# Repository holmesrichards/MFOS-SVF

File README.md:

# MFOS-SVF
Eurorack adaptation of the MFOS "Oldie But Goody" state variable filter

This is a Eurorack version of a state variable voltage controlled filter by Ray Wilson of musicfromouterspace.com. At that site there is a state variable VCF listed under "Analog Synthesizer Modules" but this project is based on another, earlier design listed under "Oldies But Goodies" at http://musicfromouterspace.com/index.php?MAINTAB=SYNTHDIY&PROJARG=OLDIESBUTGOODIES/VCF/vcfstatevar.html&VPW=2087&VPH=905.

Wilson's design was for a module in his own preferred format, with ±12V and ground soldered to the board and panel hardware mounted to the panel and wired to the board. This version has a Eurorack power connector and has panel hardware mounted to a panel PCB coupled to a main PCB with most of the circuitry.

Included in this repository are KiCad-format schematics and PCB designs for the two circuit boards, as well as an Inkscape .svg file for the panel design and a KiCad-format "PCB" for fabrication of the panel by a PCB company.

The schematics are closely based upon Wilson's original and are governed by licensing information at http://musicfromouterspace.com. The PCB layouts and panel design are new, by Richard Holmes.

BOMs are here:
https://github.com/holmesrichards/MFOS-SVF/blob/master/OBG-SVF-mainPCB/OBG-SVF-mainpcb_bom.md
and here:
https://github.com/holmesrichards/MFOS-SVF/blob/master/OBG-SVF-panelPCB/OBG-SVF-panelpcb_bom.md

## Build notes

Pretty standard. Panel PCB and main PCB joined with 2x6 pin header/socket. Use two 10 mm M3 spacers and four M3 screws to hold them together.

This time most of the components go on the panel-facing side. The power header and trimmer go on the other side. I intended the electrolytics to go on the panel-facing side but mine were too tall to fit between the boards so I mounted them on the other side.

The trimmer adjusts V/Oct response. Adjust it so a change of 1 octave (1V) on the CV input results in a change of 18 mV at the base of Q1.

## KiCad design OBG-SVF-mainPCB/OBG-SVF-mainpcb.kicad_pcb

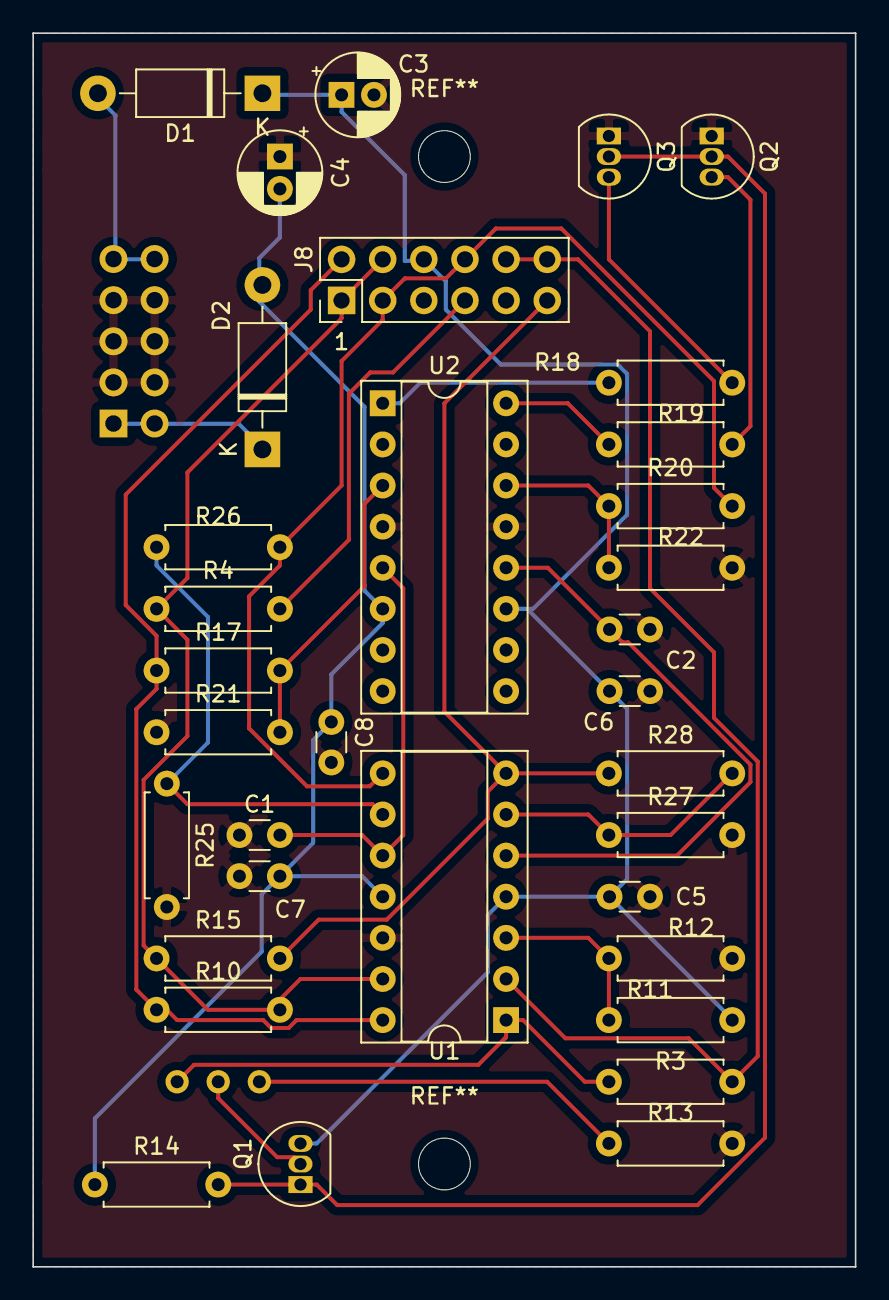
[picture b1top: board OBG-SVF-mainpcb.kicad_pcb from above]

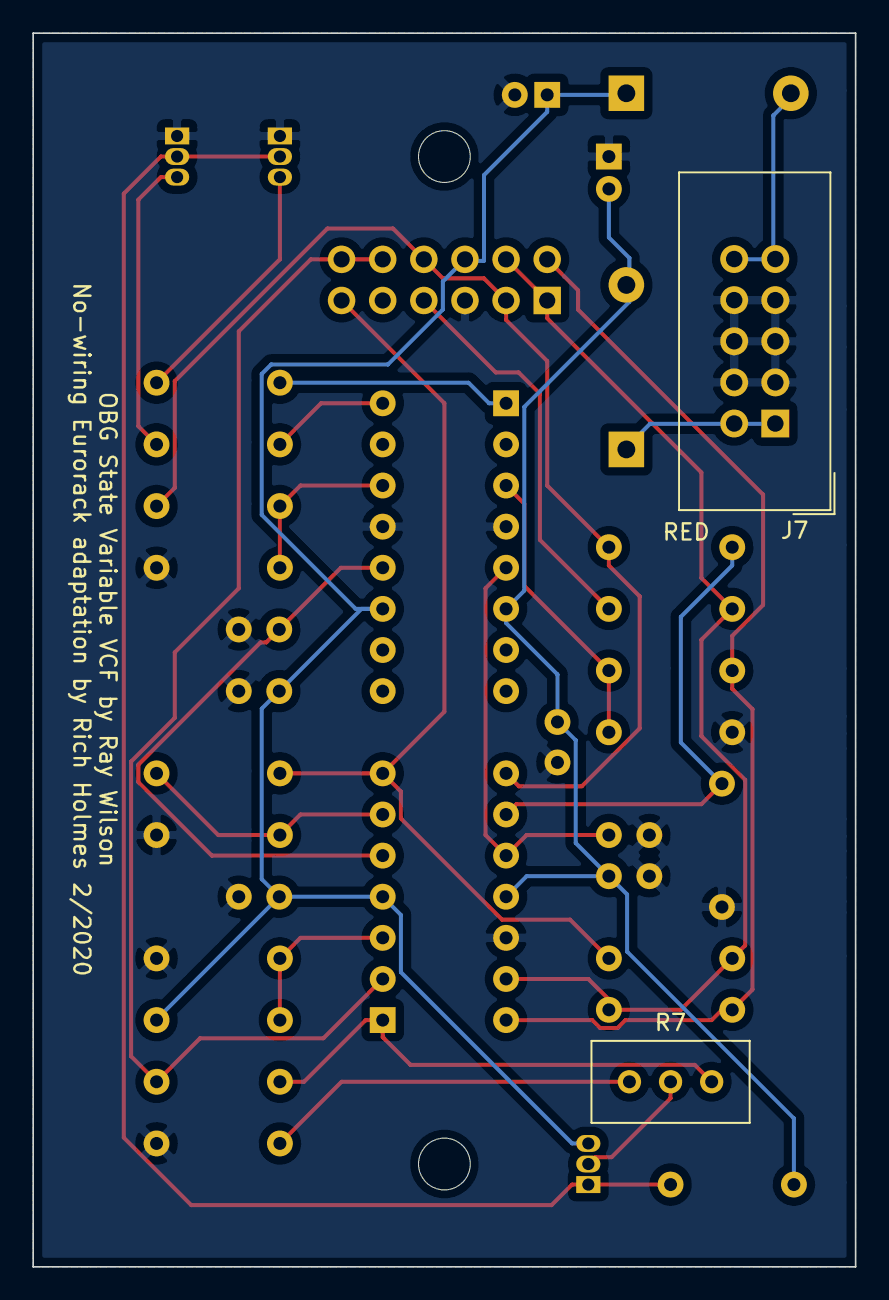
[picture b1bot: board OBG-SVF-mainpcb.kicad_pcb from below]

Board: 2 copper layers, 50.8 x 76.2 mm, 36 parts (2 on the bottom side), 26 nets.

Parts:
C1, C2: 470pF; C_Disc_D3.0mm_W1.6mm_P2.50mm
C3, C4: 10U; CP_Radial_D5.0mm_P2.00mm
C5, C6, C7, C8: 0.01U; C_Disc_D3.0mm_W1.6mm_P2.50mm
D1, D2: 1N5817; D_DO-41_SOD81_P10.16mm_Horizontal
J7: EURO_PWR_2x5; Eurorack_Power_Header_Shrouded
J8: Conn_02x06_Odd_Even; PinHeader_2x06_P2.54mm_Vertical
Q1: 2N3904; TO-92_Inline
Q2, Q3: 2N3906; TO-92_Inline
R3, R12: 2k; R_Axial_DIN0207_L6.3mm_D2.5mm_P7.62mm_Horizontal
R4, R10, R15: 47k; R_Axial_DIN0207_L6.3mm_D2.5mm_P7.62mm_Horizontal
R7: 100R; Potentiometer_Bourns_3296W_Vertical
R11, R17, R20: 100k; R_Axial_DIN0207_L6.3mm_D2.5mm_P7.62mm_Horizontal
R13: 470R; R_Axial_DIN0207_L6.3mm_D2.5mm_P7.62mm_Horizontal
R14: 120k; R_Axial_DIN0207_L6.3mm_D2.5mm_P7.62mm_Horizontal
R18, R19: 20k; R_Axial_DIN0207_L6.3mm_D2.5mm_P7.62mm_Horizontal
R21, R22: 1k; R_Axial_DIN0207_L6.3mm_D2.5mm_P7.62mm_Horizontal
R25, R27: 39k; R_Axial_DIN0207_L6.3mm_D2.5mm_P7.62mm_Horizontal
R26, R28: 150k; R_Axial_DIN0207_L6.3mm_D2.5mm_P7.62mm_Horizontal
U1: TL084; DIP-14_W7.62mm_Socket
U2: LM13700; DIP-16_W7.62mm_Socket

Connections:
+12V: C3.1, C5.2, C6.2, D1.1, J8.6, Q1.3, R11.2, U1.4, U2.11
-12V: C4.2, C7.1, C8.1, D2.2, R14.1, U1.11, U2.6
/VC: Q1.1, Q2.2, Q3.2, R14.2
BP: J8.3, J8.8, R20.2, R26.1, U1.8
CVIn: J8.10, J8.12, R3.2, U1.2
GND: C1.2, C2.1, C3.2, C4.1, C5.1, C6.1, C7.2, C8.2, J7.3, J7.4, J7.5, J7.6, J7.7, J7.8, J8.5, Q2.1, Q3.1, R12.1, R13.1, R21.1, R22.1, R25.2, R27.2, U1.12, U2.4, U2.13
HP: J8.2, R10.1, R17.1, U1.14
LP: J8.11, R15.2, R28.1, U1.7
unnamed: C1.1, U1.10, U2.5
unnamed: C2.2, U1.5, U2.12
unnamed: D1.2, J7.9, J7.10
unnamed: D2.1, J7.1, J7.2
unnamed: Q1.2, R7.2
unnamed: Q2.3, R19.1
unnamed: Q3.3, R18.1
unnamed: R3.1, R7.1, U1.1
unnamed: R11.1, R12.2, U1.3
unnamed: R7.3, R13.2
unnamed: R17.2, R21.2, U2.3
unnamed: R18.2, U2.1
unnamed: R19.2, U2.16
unnamed: R20.1, R22.2, U2.14
unnamed: R25.1, R26.2, U1.9
unnamed: R27.1, R28.2, U1.6
Res1: J8.7, R4.2
SigIn: J8.1, J8.4, R4.1, R10.2, R15.1, U1.13

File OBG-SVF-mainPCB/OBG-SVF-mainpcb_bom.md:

# OBG-SVF-mainpcb BOM

Sat 11 Apr 2020 01:31:15 PM EDT

Generated from schematic by Eeschema 5.1.5-52549c5~84~ubuntu18.04.1

**Component Count:** 36

| Value | Qty | Part | Description | Vendor |
| ----- | --- | ---- | ----------- | ------ |
| C1, C2 | 2 | 470pF | Unpolarized capacitor |  |
| C3, C4 | 2 | 10U | Polarized capacitor |  |
| C5, C6, C7, C8 | 4 | 0.1uF | Unpolarized capacitor |  |
| D1, D2 | 2 | 1N5817 | 20V 1A Schottky Barrier Rectifier Diode, DO-41 |  |
| J7 | 1 | EURO_PWR_2x5 | Eurorack style 2x5 pin power header |  |
| J8 | 1 | Conn_02x06_Odd_Even | Generic connector, double row, 02x06 |  |
| Q1 | 1 | 2N3904 | 0.2A Ic, 40V Vce, Small Signal NPN Transistor, TO-92 |  |
| Q2, Q3 | 2 | 2N3906 | -0.2A Ic, -40V Vce, Small Signal PNP Transistor, TO-92 |  |
| R3, R12 | 2 | 2k | Resistor |  |
| R4, R10, R15 | 3 | 47k | Resistor |  |
| R7 | 1 | 100R | Trim-potentiometer |  |
| R11, R17, R20 | 3 | 100k | Resistor |  |
| R13 | 1 | 470R | Resistor |  |
| R14 | 1 | 120k | Resistor |  |
| R18, R19 | 2 | 20k | Resistor |  |
| R21, R22 | 2 | 1k | Resistor |  |
| R25, R27 | 2 | 39k | Resistor |  |
| R26, R28 | 2 | 150k | Resistor |  |
| U1 | 1 | TL084 | Quad JFET-Input Operational Amplifiers, DIP-14 |  |
| U2 | 1 | LM13700 | Dual Operational Transconductance Amplifiers with Linearizing Diodes and Buffers, DIP-16 |  |

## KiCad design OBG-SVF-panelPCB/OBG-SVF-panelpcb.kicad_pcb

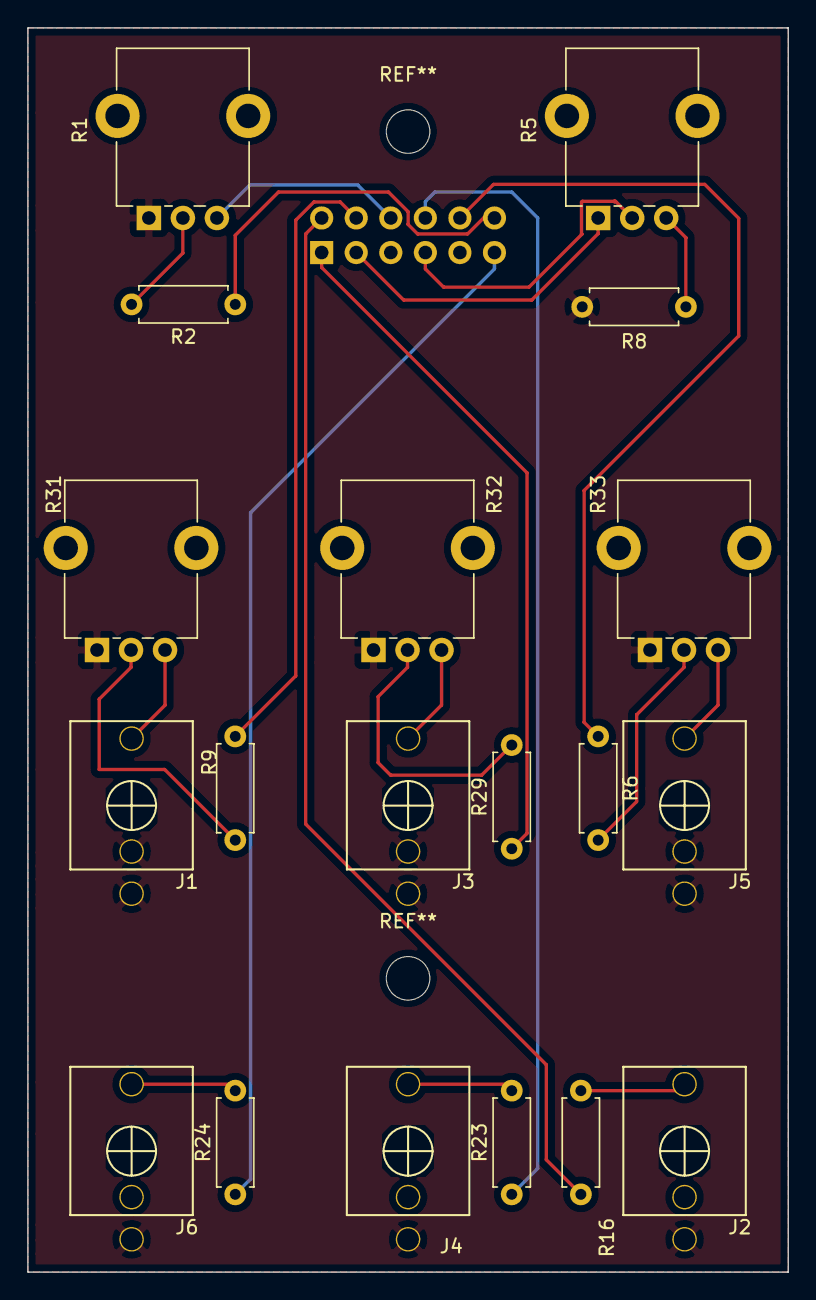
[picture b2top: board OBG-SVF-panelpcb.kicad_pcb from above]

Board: 2 copper layers, 55.9 x 91.4 mm, 20 parts (1 on the bottom side), 22 nets.

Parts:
J1, J2, J3, J4, J5, J6: AudioJack2; PJ301M-12
J9: Conn_02x06_Odd_Even; PinSocket_2x06_P2.54mm_Vertical
R1, R5, R31, R32, R33: 100k; Potentiometer_Alpha_RD901F-40-00D_Single_Vertical_CircularH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
R2, R6: 100k; R_Axial_DIN0207_L6.3mm_D2.5mm_P7.62mm_Horizontal
R8: 9.1k; R_Axial_DIN0207_L6.3mm_D2.5mm_P7.62mm_Horizontal
R9, R29: 270k; R_Axial_DIN0207_L6.3mm_D2.5mm_P7.62mm_Horizontal
R16, R23, R24: 1k; R_Axial_DIN0207_L6.3mm_D2.5mm_P7.62mm_Horizontal

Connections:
+12V: J9.6, R1.3
BP: J9.8, R23.1
CVIn: J9.10, R6.1
GND: J1.1, J1.2, J2.1, J3.1, J3.2, J4.1, J5.1, J5.2, J6.1, J9.5, R1.1, R8.1, R31.1, R32.1, R33.1
HP: J9.2, R16.2
LP: J9.11, R24.1
unnamed: J1.3, R31.3
unnamed: J2.3, R16.1
unnamed: J3.3, R32.3
unnamed: J4.3, R23.2
unnamed: J5.3, R33.3
unnamed: J6.3, R24.2
unnamed: R1.2, R2.2
unnamed: R5.3, R8.2
unnamed: R29.2, R32.2
unnamed: R9.2, R31.2
unnamed: R6.2, R33.2
R1(2): J9.12, R2.1
Res1: J9.7, R5.2
Res2: J9.3, R5.1
SigIn: J9.4, R9.1
SigIn2: J9.1, R29.1

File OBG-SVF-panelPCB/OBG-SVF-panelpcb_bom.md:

# OBG-SVF-panelpcb BOM

Sat 11 Apr 2020 01:33:45 PM EDT

Generated from schematic by Eeschema 5.1.5-52549c5~84~ubuntu18.04.1

**Component Count:** 20

| Value | Qty | Part | Description | Vendor |
| ----- | --- | ---- | ----------- | ------ |
| J1, J2, J3, J4, J5, J6 | 6 | AudioJack2 |  |  |
| J9 | 1 | Conn_02x06_Odd_Even | Generic connector, double row, 02x06, odd/even pin numbering scheme (row 1 odd numbers, row 2 even numbers), script generated (kicad-library-utils/schlib/autogen/connector/) |  |
| R1, R5, R31, R32, R33 | 5 | 100k | Potentiometer |  |
| R2, R6 | 2 | 100k | Resistor |  |
| R8 | 1 | 9.1k | Resistor |  |
| R9, R29 | 2 | 270k | Resistor |  |
| R16, R23, R24 | 3 | 1k | Resistor |  |
    
*Additional parts not on schematic:*

| Qty | Part | Description |
| --- | ---- | ----------- |
|   2 | 10 mm x M3 | Spacer |
|   4 | M3 | Screw |
|   5 |   | Knob |

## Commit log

2020-02-23 Initial version
2020-02-23 Expand upon roles of Wilson and Holmes
2020-02-23 Move licensing
2020-02-23 Create LICENSE
2020-03-18 Panel PCB Gerbers, some schematic updates
2020-03-18 main PCB and panel Gerbers
2020-03-24 Fix bypass capacitors
2020-04-11 BOM links
2020-04-11 Build notes
2020-04-11 Images (and a random Inkscape change)
2020-04-11 Add picture
2020-04-11 Markdown BOMs
2020-04-12 Move global library to local
2020-09-01 Belated commit of various updates
2021-01-17 Include lib table files
